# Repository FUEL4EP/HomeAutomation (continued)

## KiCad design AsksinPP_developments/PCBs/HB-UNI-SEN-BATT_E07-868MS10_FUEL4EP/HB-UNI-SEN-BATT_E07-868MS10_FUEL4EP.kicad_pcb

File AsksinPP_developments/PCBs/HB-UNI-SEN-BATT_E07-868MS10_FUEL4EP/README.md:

# HB-UNI-SEN-BATT_E07-868MS10_FUEL4EP  

**Platine für DIY AsksinPP Projekte basierend auf den folgenden möglichen Arduino-Modulen:**
- [Arduino Pro Mini 328 - 3.3V/8MHz](https://www.sparkfun.com/arduino-pro-mini-328-3-3v-8mhz.html): 32kByte Programmspeicher, 4kByte SRAM, 1kByte EEPROM
- NEU: [HB_Pro_Mini_ATMEGA1284P_FUEL4EP](https://github.com/FUEL4EP/HomeAutomation/tree/master/AsksinPP_developments/PCBs/HB_Pro_Mini_ATMEGA1284P_FUEL4EP)
	+ mit deutlich mehr Programm-, RAM- und EEPROM-Speicher als Arduino Pro Mini: 128kByte Programmspeicher, 16kByte SRAM, 4kByte EEPROM)
- [Tindie Pro Mini XL - v2 - ATmega 1284p](https://www.tindie.com/products/prominimicros/pro-mini-xl-v2-atmega-1284p/)
	+ mit deutlich mehr Programm-, RAM- und EEPROM-Speicher als Arduino Pro Mini: 128kByte Programmspeicher, 16kByte SRAM, 4kByte EEPROM)

## Credits

- diese Platine ist von Alexander Reinerts Platine [HB-UNI-SEN-BATT](https://github.com/alexreinert/PCB/tree/master/HB-UNI-SEN-BATT) abgeleitet.
- vielen Dank an Alexander Reinert für die Vorarbeit.

## Status der Validierung der Platine

- Platine wurde bis zur Version V1.3 bei JLCPCB erfolgreich gefertigt und validiert
- der Prototyp der neuen Platinenversion V1.4 wurde bei JLCPCB gefertigt, von Hand bestückt, verlötet und erfolgreich mit dem Sketch [HB-UNI-SENSOR1-AQ-BME680_KF_rLF](https://github.com/FUEL4EP/HomeAutomation/tree/master/AsksinPP_developments/sketches/HB-UNI-Sensor1-AQ-BME680_KF_rLF) validiert:
	
- Als Funkmodul wurde der [Adapter_EByte_E07_900MM10S_to_Ebyte_E07_868MS10_FUEL4EP](https://github.com/FUEL4EP/HomeAutomation/tree/master/AsksinPP_developments/PCBs/Adapter_EByte_E07_900MM10S_to_Ebyte_E07_868MS10_FUEL4EP) verwendet.

## Eigenschaften

- Weiterentwicklung von [HB-UNI-SEN-BATT](https://github.com/alexreinert/PCB/tree/master/HB-UNI-SEN-BATT) mit denselben Außenmaßen
- neue Eigenschaften:
	+ alternativ werden verschiedene Arduino Module unterstützt:
		- [Arduino Pro Mini 328 - 3.3V/8MHz](https://www.sparkfun.com/arduino-pro-mini-328-3-3v-8mhz.html): 32kByte Programmspeicher, 4kByte SRAM, 1kByte EEPROM
		- [HB_Pro_Mini_ATMEGA1284P_FUEL4EP](https://github.com/FUEL4EP/HomeAutomation/tree/master/AsksinPP_developments/PCBs/HB_Pro_Mini_ATMEGA1284P_FUEL4EP)
			+ mit deutlich mehr Programm-, RAM- und EEPROM-Speicher als Arduino Pro Mini: 128kByte Programmspeicher, 16kByte SRAM, 4kByte EEPROM)
			+ mit optionalem Boost-Konverter für Betrieb mit NiMH-Akkumulatoren oder nur einer AA Alkaline Battterie
		- [Tindie Pro Mini XL - v2 - ATmega 1284p](https://www.tindie.com/products/prominimicros/pro-mini-xl-v2-atmega-1284p/)
			+ mit deutlich mehr Programm-, RAM- und EEPROM-Speicher als Arduino Pro Mini: 128kByte Programmspeicher, 16kByte SRAM, 4kByte EEPROM

    + nur eine LED
    + dafür optionale Unterstützung von Akkumulatorbetrieb mit einem externen 'Huckepack' Aufwärtswandlermodul (siehe z.B. [HB-UNI-SENSOR1-CO2-SCD30](https://github.com/FUEL4EP/HomeAutomation/tree/master/AsksinPP_developments/sketches/HB-UNI-Sensor1-CO2_SCD30)
    + Stiftleiste J10 mit Versorgungsspannungen zum Gehäuseoberteil oder Akkulademodul
    + Korrektur der Abstandfehlers bei einem Batteriehalter. Beim [HB-UNI-SEN-BATT](https://github.com/alexreinert/PCB/tree/master/HB-UNI-SEN-BATT) hat das schon mal gerne zu thermischen Ausfällen durch mechanische Spannungen geführt.

### Benötigte Bauteile:
* eines der folgenden Arduino Module
	- [Arduino Pro Mini 328 - 3.3V/8MHz](https://www.sparkfun.com/arduino-pro-mini-328-3-3v-8mhz.html)
	- [HB_Pro_Mini_ATMEGA1284P_FUEL4EP](https://github.com/FUEL4EP/HomeAutomation/tree/master/AsksinPP_developments/PCBs/HB_Pro_Mini_ATMEGA1284P_FUEL4EP)
	- [Tindie Pro Mini XL - v2 - ATmega 1284p](https://www.tindie.com/products/prominimicros/pro-mini-xl-v2-atmega-1284p/)
*  [eByte E07-868MS10 Sendemodul 868MHz](https://www.elecbee.com/de-24376-E07-868MS10-CC1101-Stamp-Hole-Antenna-IoT-UHF-1000m-868MHz-SPI-10dBm-Wireless-Transmitter-Transceiver-RF-Module) oder alternativ das [Elecbee CC1101 Wireless-Modul 868 MHz](https://www.elecbee.com/de-24507-CC1101-Wireless-Module-868MHz-Digital-Transmission-Receiving-Industrial-grade-RF-Communication-Transparent-Transmission) Modul
* 1x LEDs 3mm Low Current (Pin 4)
* 1x 470Ohm Widerstände (Vorwiderstand für LED)
* Elko 10uF 1,5mm
* 2x Keystone 2460 Batteriehalter 1xAA (oder Goobay 1xAA Batteriehalter)
* Mikroschalter 6*6mm
* Stiftleiste RM 1.27mm 1x8 Pin (für eByte E07-868MS10 Modul)
* Stiftleisten RM 2,54mm (nach Bedarf)
* IRLU024N (optional für Verpolungsschutz)
* 100KOhm Widerstand (optional für Verpolungsschutz)
* 2x 10KOhm Widerstand (Pullup für I2C)

### Aufbauhinweise

- es wird dringend angeraten, vor dem Einbau der I2C Sensoren durchzuführen
    + einen Frequenztest. Hier der Frequenztest für einen [Tindie Pro Mini XL - v2 - ATmega 1284p](https://www.tindie.com/products/prominimicros/pro-mini-xl-v2-atmega-1284p/) : [FreqTest_1284P.ino](../Supplements/FreqTest_1284P/FreqTest_1284P.ino)
    + einen Leckstromtest. Hier der Leckstromtest für einen [Tindie Pro Mini XL - v2 - ATmega 1284p](https://www.tindie.com/products/prominimicros/pro-mini-xl-v2-atmega-1284p/) : [SleepTest_1284P.ino](../Supplements/SleepTest_1284P/SleepTest_1284P.ino)
        + der Leckstrom im Sleepmode sollte < 10 uA betragen
    + für einen Arduino Pro Mini die entsprechenden Standardsketche für den Frequenztest und den SleepTest verwenden.
    + am besten diese beiden Tests in einem Testaufbau mit Stecksockeln vor dem Einlöten durchführen

## Konfiguration der Überbrückungen

- bitte die Platinenüberbrückungen vor Inbetriebnahme je nach gewählter Hardwarekonfiguration wählen:

- die Tabellen dazu sind [hier](./Jumper_settings) zu finden
    
## lokale Installation des Github Releases auf Deinem Computer

- gehe bitte in Dein Zielinstallationsverzeichnis, wo Du mit der HB-UNI-SEN-BATT_E07-868MS10_FUEL4EP Platine mit KiCAD arbeiten möchtest

  - gebe dort 'git clone https://github.com/FUEL4EP/HomeAutomation.git' ein
	  + damit lädst Du mein [Sammelrepository](https://github.com/FUEL4EP/HomeAutomation) für alle meine auf Github freigegebenen HomeBrew Entwicklungen herunter.
  - dann findest Du ein neues Verzeichnis 'HomeAutomation' auf Deinem Rechner, das alle meine auf Github freigebenen Entwicklungen enthält, siehe [README.md](https://github.com/FUEL4EP/HomeAutomation/blob/master/README.md)
  	+ mache bitte regelmäßig ein Update mit 'git pull'
 -	die Platine HB-UNI-SEN-BATT_E07-868MS10_FUEL4EP findest Du unter './HomeAutomation/tree/master/AsksinPP_developments/PCBs/HB-UNI-SEN-BATT_E07-868MS10_FUEL4EP'
 
- alternativ kann vom Github [Sammelrepository](https://github.com/FUEL4EP/HomeAutomation) die ZIP-Datei HomeAutomation-master.zip heruntergeladen und auf dem lokalen Rechner ausgepackt werden. Bitte dann regelmäßig auf Github nach Updates schauen.

### Passende AsksinPP Projekte von FUEL4EP
- Arduino Pro Mini ATMega328P oder Tindie Pro Mini XL - v2 - ATmega 1284p basierend:
    + [HB-UNI-Sensor1-THPD-BME280](https://github.com/FUEL4EP/HomeAutomation/tree/master/AsksinPP_developments/sketches/HB-UNI-Sensor1-THPD-BME280)
    + [HB-UNI-Sensor1-TH-SHT75](https://github.com/FUEL4EP/HomeAutomation/tree/master/AsksinPP_developments/sketches/HB-UNI-Sensor1-TH-SHT75)
     + [HB-UNI-Sensor1-CO2_SCD30](https://github.com/FUEL4EP/HomeAutomation/tree/master/AsksinPP_developments/sketches/HB-UNI-Sensor1-CO2_SCD30)
- [HB_Pro_Mini_ATMEGA1284P_FUEL4EP](https://github.com/FUEL4EP/HomeAutomation/tree/master/AsksinPP_developments/PCBs/HB_Pro_Mini_ATMEGA1284P_FUEL4EP) oder [Tindie Pro Mini XL - v2 - ATmega 1284p](https://www.tindie.com/products/prominimicros/pro-mini-xl-v2-atmega-1284p/) basierend:
     + [HB-UNI-Sensor1-AQ-BME680](https://github.com/FUEL4EP/HomeAutomation/tree/master/AsksinPP_developments/sketches/HB-UNI-Sensor1-AQ-BME680)
    + [HB-UNI-Sensor1-AQ-BME680_KF](https://github.com/FUEL4EP/HomeAutomation/tree/master/AsksinPP_developments/sketches/HB-UNI-Sensor1-AQ-BME680_KF)
    + [HB-UNI-Sensor1-AQ-BME680_KF_DEBUG](https://github.com/FUEL4EP/HomeAutomation/tree/master/AsksinPP_developments/sketches/HB-UNI-Sensor1-AQ-BME680_KF_DEBUG)
    + [HB-UNI-Sensor1-RAD-AL53](https://github.com/FUEL4EP/HomeAutomation/tree/master/AsksinPP_developments/sketches/HB-UNI-Sensor1-RAD-AL53)
    + [HB-UNI-Sensor1-THPD-SHT85](https://github.com/FUEL4EP/HomeAutomation/tree/master/AsksinPP_developments/sketches/HB-UNI-Sensor1-THPD-SHT85)

### Passendes Gehäuse
* Camdenboss CBRS01SWH und CBRS01VWH
* oder [Gehäuse HB-UNI-SEN-BATT snap in V2 von wpatrick](https://www.thingiverse.com/thing:3540481) für 3D-Druck

### Hinweise
* Achtung: Kein Überspannungschutz vorhanden
* der Verpolungsschutz ist optional. Dafür Bauteil Q1 (IRLU024N) und R3 (100KOhm Widerstand) bestücken. Alternativ JP1 auf der Platinenrückseite überbrücken, um ohne Verpolungsschutz zu arbeiten.

### KiCAD Plugin
- für die Erzeugung der JLCPCB Produktionsdaten wurde das Plugin [KiCAD JLCPCB tools](https://github.com/bouni/kicad-jlcpcb-tools) verwendet.

## Bestellen von Platinen

- die Platine kann entweder direkt bei JLCPCB bestellt werden
- die notwendigen Produktionsdaten stehen [hier](./jlcpcb/production_files/)
- oder per PN bei [FUEL4EP](https://homematic-forum.de/forum/ucp.php?i=pm&mode=compose&u=20685) im Homematic Forum nachfragen. Aus der Bestellung der Prototypen sind noch Platinen kostengünstig abzugeben (Stand 13. Juli 2023).
	
## passende DIY I2C-Sensormodule für die Fertigung bei JLCPCB
- als DIY-Ersatz für kommerzielle Sensormodule stehen folgende passende Adapterplatinen zur Verfügung:
	- [I2C_Module_BME280_FUEL4EP](https://github.com/FUEL4EP/HomeAutomation/tree/master/AsksinPP_developments/PCBs/I2C_Module_BME280_FUEL4EP)
	- [I2C_Module_BME680_FUEL4EP](https://github.com/FUEL4EP/HomeAutomation/tree/master/AsksinPP_developments/PCBs/I2C_Module_BME680_FUEL4EP)
	- [I2C_Module_SHT85_BME280_FUEL4EP](https://github.com/FUEL4EP/HomeAutomation/tree/master/AsksinPP_developments/PCBs/I2C_Module_SHT85_BME280_FUEL4EP)
	- [I2C_Module_SHT45_BME280_FUEL4EP](https://github.com/FUEL4EP/HomeAutomation/tree/master/AsksinPP_developments/PCBs/I2C_Module_SHT45_BME280_FUEL4EP)
	- [4Bit_I2C_Port_Expander_Module_FUEL4EP](https://github.com/FUEL4EP/HomeAutomation/tree/master/AsksinPP_developments/PCBs/4Bit_I2C_Port_Expander_Module_FUEL4EP)

## Versionen
- KiCad Schaltplan-Editor Version: 8.0.9-8.0.9-0~ubuntu22.04.1, release build unter Kubuntu22.04.1
- KiCad Leiterplatteneditor Version: 8.0.9-8.0.9-0~ubuntu22.04.1, release build unter Kubuntu22.04.1 1.
- aktuelle PCB Version 1.4 
- aktuelle Schematics Version 1.3 

## Disclaimer

-  die Nutzung der hier veröffentlichten Inhalte erfolgt vollständig auf eigenes Risiko und ohne jede Gewähr.

## Lizenz 

**Creative Commons BY-NC-SA**<br>
Give Credit, NonCommercial, ShareAlike

<br />This work is licensed under a <a rel="license" href="http://creativecommons.org/licenses/by-nc-sa/4.0/">Creative Commons Attribution-NonCommercial-ShareAlike 4.0 International License</a>.

-EOF

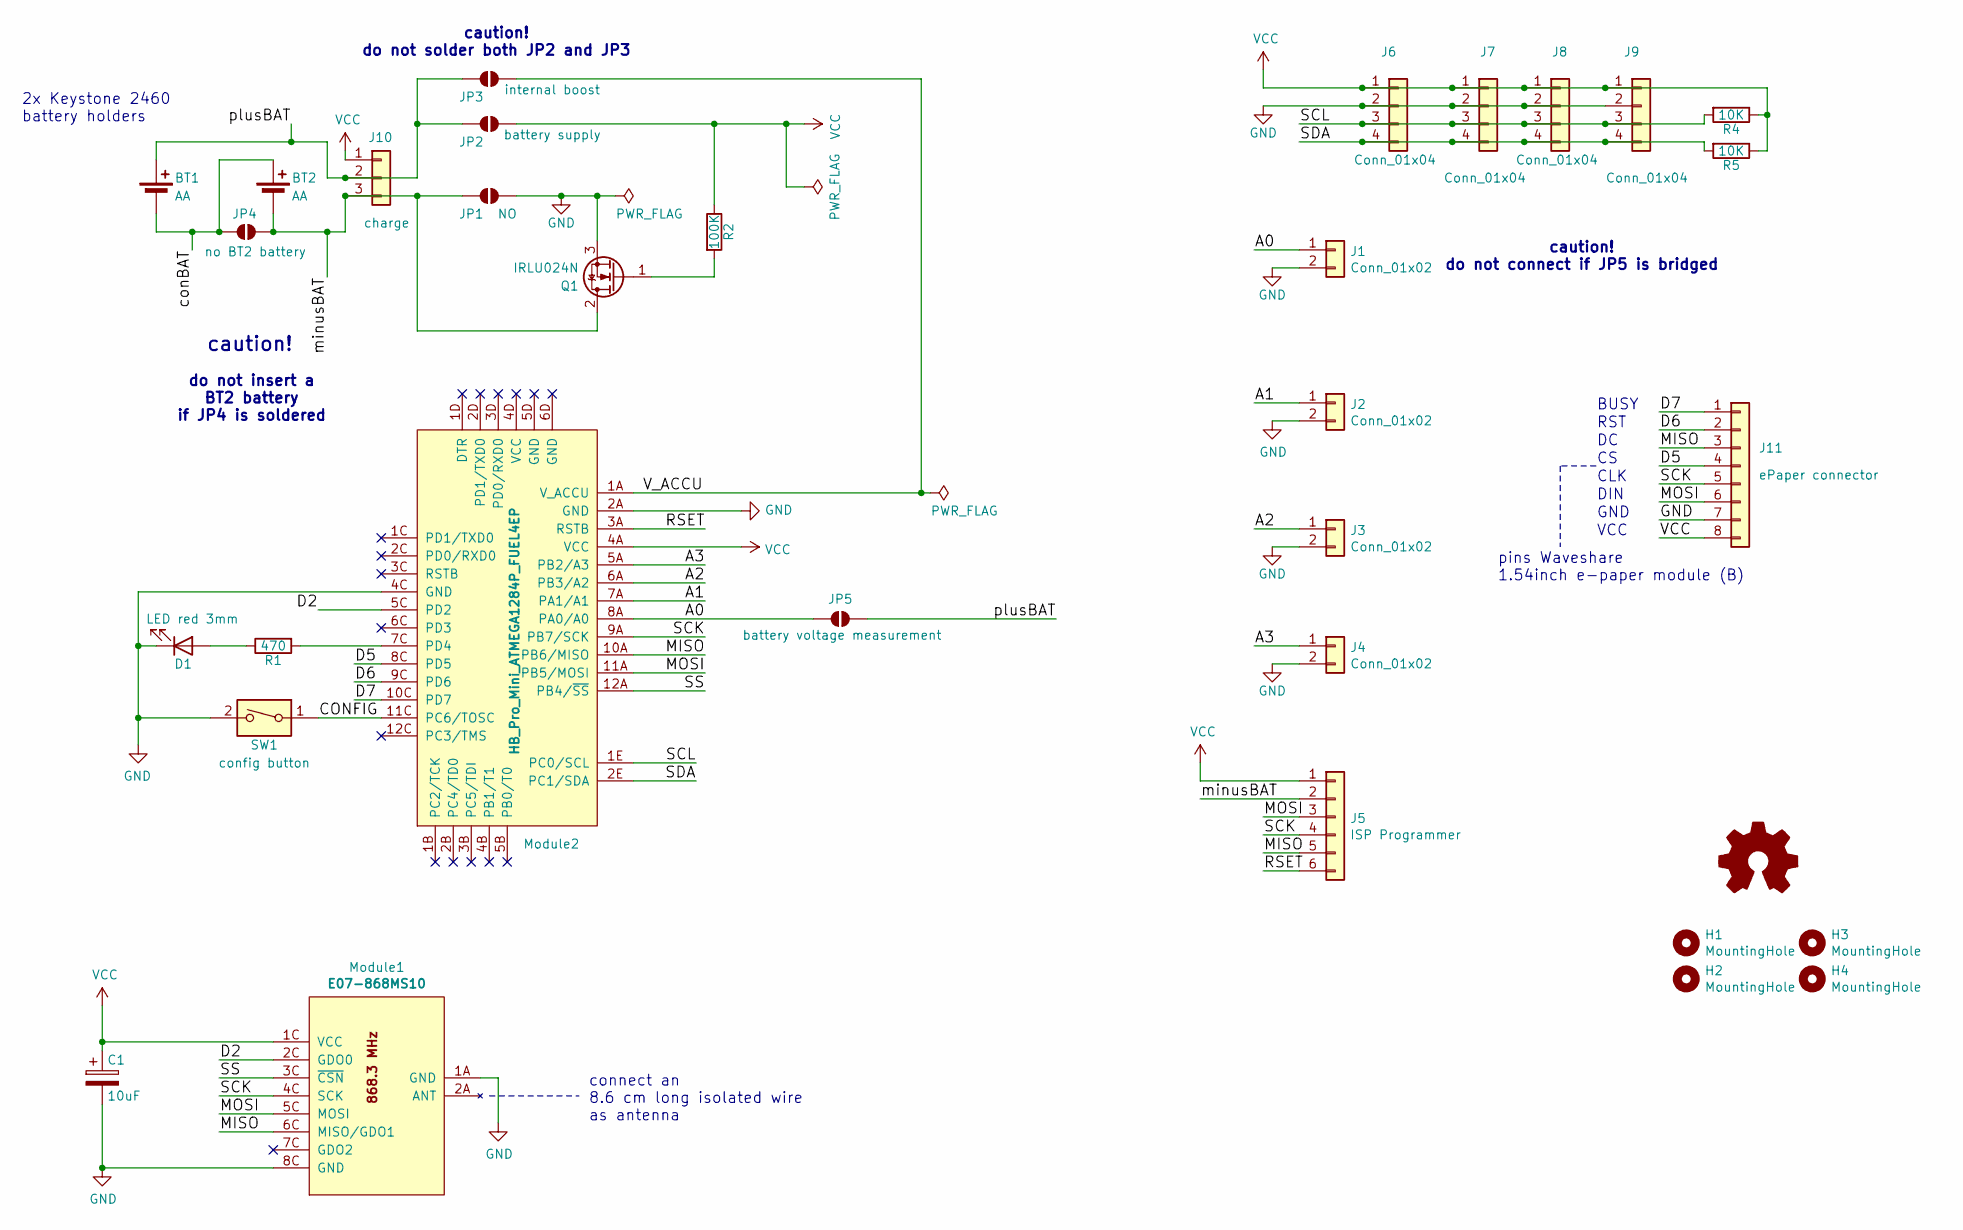
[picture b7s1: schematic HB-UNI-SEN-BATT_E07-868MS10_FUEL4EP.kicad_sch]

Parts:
BT1, BT2: AA; BatteryHolder_Keystone_2460_1xAA
C1: 10uF; CP_Radial_D4.0mm_P1.50mm
D1: LED red 3mm; LED_D3.0mm
H1, H2, H3, H4: MountingHole; MountingHole_2.2mm_M2_Pad_Via
J1, J2, J3, J4: Conn_01x02; PinHeader_1x02_P2.54mm_Vertical
J5: ISP Programmer; PinHeader_1x06_P2.54mm_Vertical
J6, J7, J8, J9: Conn_01x04; PinHeader_1x04_P2.54mm_Vertical
J10: charge; PinHeader_1x03_P2.54mm_Vertical
J11: ePaper connector; PinPads_1x08_P2.00mm_Vertical
JP1: NO; SolderJumper-2_P1.3mm_Open_Pad1.0x1.5mm
JP2: battery supply; SolderJumper-2_P1.3mm_Open_Pad1.0x1.5mm
JP3: internal boost; SolderJumper-2_P1.3mm_Open_Pad1.0x1.5mm
JP4: no BT2 battery; SolderJumper-2_P1.3mm_Open_Pad1.0x1.5mm
JP5: battery voltage measurement; SolderJumper-2_P1.3mm_Open_Pad1.0x1.5mm
LOGO1: Logo_Open_Hardware_Small; CC-BY-ND-SA
Module1: E07-868MS10; eByte_E07-868MS10
Module2: HB_Pro_Mini_ATMEGA1284P_FUEL4EP
Q1: IRLU024N; TO-251-3_Vertical
R1: 470; R_Axial_DIN0207_L6.3mm_D2.5mm_P2.54mm_Vertical
R2: 100K; R_Axial_DIN0207_L6.3mm_D2.5mm_P2.54mm_Vertical
R4, R5: 10K; R_Axial_DIN0207_L6.3mm_D2.5mm_P2.54mm_Vertical
SW1: config button; SW_PUSH_6mm_H5mm

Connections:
/A0: J1.1, JP5.1 (A), Module2.8A (PA0/A0)
/A1: J2.1, Module2.7A (PA1/A1)
/A2: J3.1, Module2.6A (PB3/A2)
/A3: J4.1, Module2.5A (PB2/A3)
/CONFIG: Module2.11C (PC6/TOSC), SW1.1
/D2: Module1.2C (GDO0), Module2.5C (PD2)
/D5: J11.4, Module2.8C (PD5)
/D6: J11.2, Module2.9C (PD6)
/D7: J11.1, Module2.10C (PD7)
/MISO: J5.5, J11.3, Module1.6C (MISO/GDO1), Module2.10A (PB6/MISO)
/MOSI: J5.3, J11.6, Module1.5C (MOSI), Module2.11A (PB5/MOSI)
/RSET: J5.6, Module2.3A (RSTB)
/SCK: J5.4, J11.5, Module1.4C (SCK), Module2.9A (PB7/SCK)
/SCL: J6.3, J7.3, J8.3, J9.3, Module2.1E (PC0/SCL), R4.2
/SDA: J6.4, J7.4, J8.4, J9.4, Module2.2E (PC1/SDA), R5.2
/SS: Module1.3C (~CSN), Module2.12A (PB4/~SS)
/V_ACCU: JP3.2 (B), Module2.1A (V_ACCU)
/conBAT: BT1.2 (-), BT2.1 (+), JP4.1 (A)
/minusBAT: BT2.2 (-), J5.2, J10.3, JP1.1 (A), JP4.2 (B), Q1.2 (D)
/plusBAT: BT1.1 (+), J10.2, JP2.1 (A), JP3.1 (A), JP5.2 (B)
GND: C1.2, D1.1 (K), J1.2, J2.2, J3.2, J4.2, J6.2, J7.2, J8.2, J9.2, J11.7, JP1.2 (B), Module1.1A (GND), Module1.8C (GND), Module2.2A (GND), Module2.4C (GND), Q1.3 (S), SW1.2
unnamed: D1.2 (A), R1.1
unnamed: Module2.7C (PD4), R1.2
unnamed: Q1.1 (G), R2.2
VCC: C1.1, J5.1, J6.1, J7.1, J8.1, J9.1, J10.1, J11.8, JP2.2 (B), Module1.1C (VCC), Module2.4A (VCC), R2.1, R4.1, R5.1

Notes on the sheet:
VCC
DIN
connect an 8.6 cm long isolated wire as antenna
BUSY
2x Keystone 2460 battery holders
GND
CLK
caution! do not connect if JP5 is bridged
caution!
RST
do not insert a BT2 battery if JP4 is soldered
caution! do not solder both JP2 and JP3
pins Waveshare 1.54inch e-paper module (B)

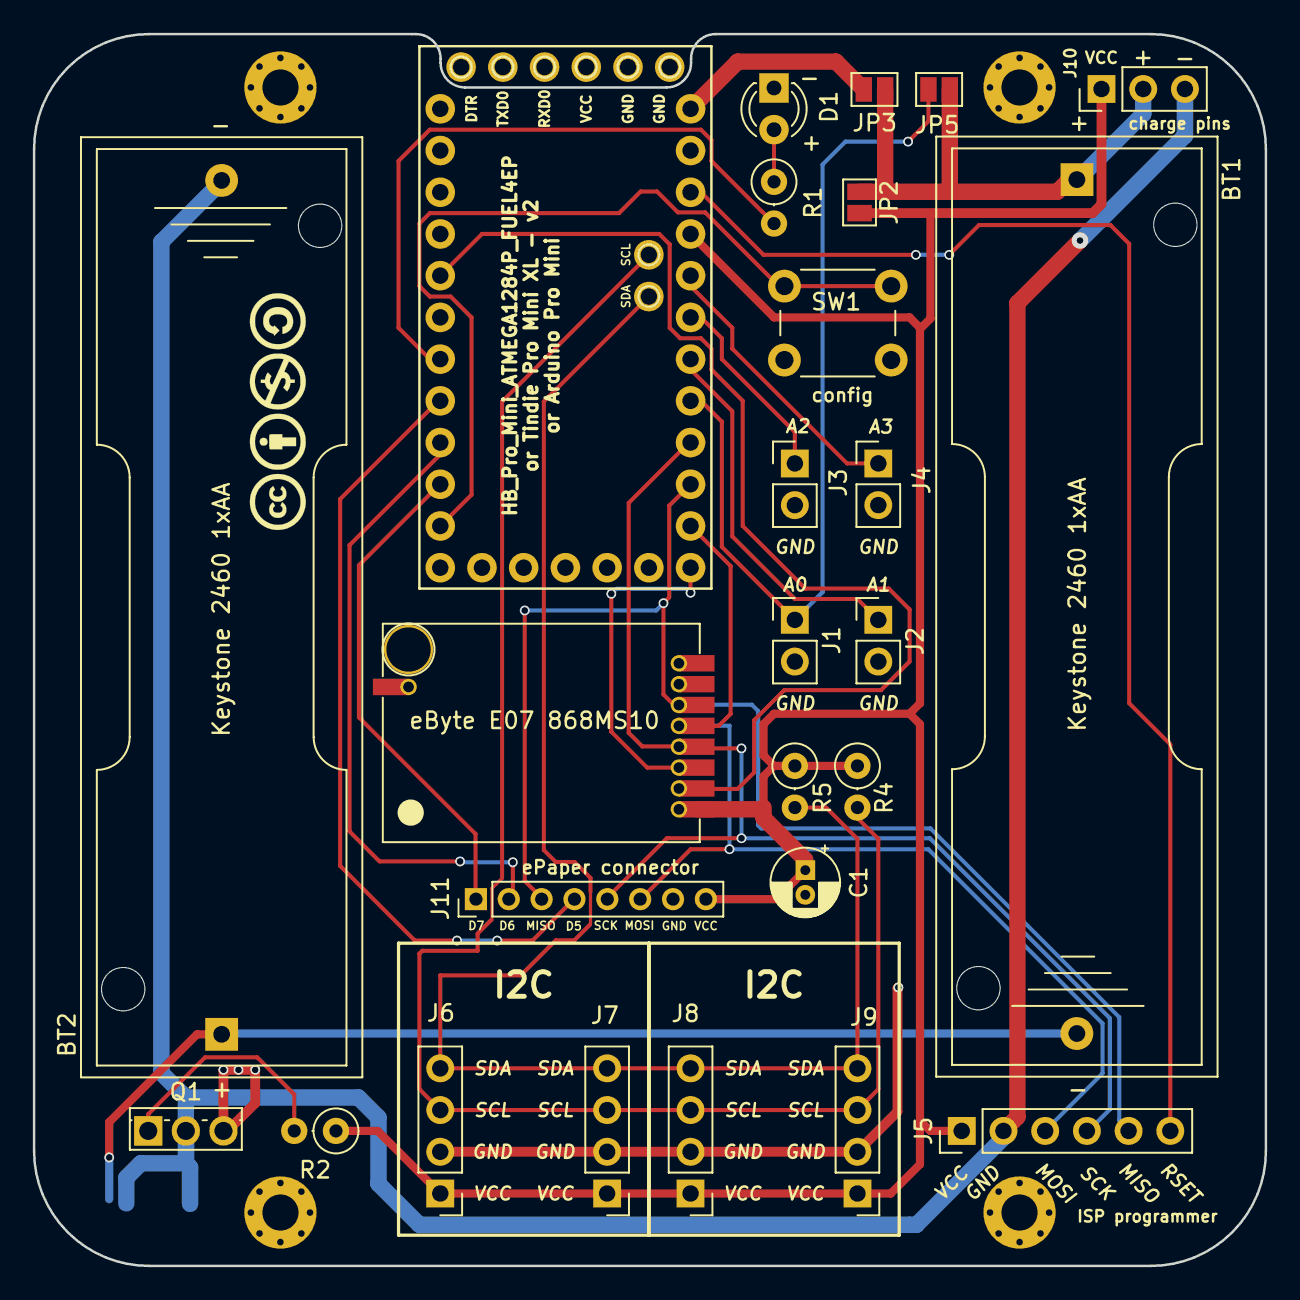
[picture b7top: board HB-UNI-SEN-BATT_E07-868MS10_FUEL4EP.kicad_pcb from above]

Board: 2 copper layers, 75.0 x 75.0 mm, 33 parts (0 on the bottom side), 25 nets.

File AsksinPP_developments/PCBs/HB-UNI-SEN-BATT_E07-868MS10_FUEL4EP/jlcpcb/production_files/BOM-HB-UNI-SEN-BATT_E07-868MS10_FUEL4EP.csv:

Comment,Designator,Footprint,LCSC,Quantity
LED red 3mm,D1,LED_D3.0mm,,1
Conn_01x02,J1,PinHeader_1x02_P2.54mm_Vertical,,1
Conn_01x02,J2,PinHeader_1x02_P2.54mm_Vertical,,1
Conn_01x04,J7,PinHeader_1x04_P2.54mm_Vertical,,1
AA,BT1,BatteryHolder_Keystone_2460_1xAA,,1
Conn_01x02,J3,PinHeader_1x02_P2.54mm_Vertical,,1
Conn_01x02,J4,PinHeader_1x02_P2.54mm_Vertical,,1
ISP Programmer,J5,PinHeader_1x06_P2.54mm_Vertical,,1
Conn_01x04,J6,PinHeader_1x04_P2.54mm_Vertical,,1
10uF,C1,CP_Radial_D4.0mm_P1.50mm,,1
10K,R4,R_Axial_DIN0207_L6.3mm_D2.5mm_P2.54mm_Vertical,,1
10K,R5,R_Axial_DIN0207_L6.3mm_D2.5mm_P2.54mm_Vertical,,1
470,R1,R_Axial_DIN0207_L6.3mm_D2.5mm_P2.54mm_Vertical,,1
IRLU024N,Q1,TO-251-3_Vertical,,1
Conn_01x04,J9,PinHeader_1x04_P2.54mm_Vertical,,1
charge,J10,PinHeader_1x03_P2.54mm_Vertical,,1
NO,JP1,SolderJumper-2_P1.3mm_Open_Pad1.0x1.5mm,,1
HB_Pro_Mini_ATMEGA1284P_FUEL4EP,Module2,HB_Pro_Mini_ATMEGA1284P_FUEL4EP,,1
E07-868MS10,Module1,eByte_E07-868MS10,,1
battery supply,JP2,SolderJumper-2_P1.3mm_Open_Pad1.0x1.5mm,,1
config button,SW1,SW_PUSH_6mm_H5mm,,1
Conn_01x04,J8,PinHeader_1x04_P2.54mm_Vertical,,1
MountingHole,H2,MountingHole_2.2mm_M2_Pad_Via,,1
MountingHole,H4,MountingHole_2.2mm_M2_Pad_Via,,1
MountingHole,H1,MountingHole_2.2mm_M2_Pad_Via,,1
MountingHole,H3,MountingHole_2.2mm_M2_Pad_Via,,1
Logo_Open_Hardware_Small,LOGO1,CC-BY-ND-SA,,1
ePaper connector,J11,PinPads_1x08_P2.00mm_Vertical,,1
AA,BT2,BatteryHolder_Keystone_2460_1xAA,,1
100K,R2,R_Axial_DIN0207_L6.3mm_D2.5mm_P2.54mm_Vertical,,1
battery voltage measurement,JP5,SolderJumper-2_P1.3mm_Open_Pad1.0x1.5mm,,1
no BT2 battery,JP4,SolderJumper-2_P1.3mm_Open_Pad1.0x1.5mm,,1
internal boost,JP3,SolderJumper-2_P1.3mm_Open_Pad1.0x1.5mm,,1

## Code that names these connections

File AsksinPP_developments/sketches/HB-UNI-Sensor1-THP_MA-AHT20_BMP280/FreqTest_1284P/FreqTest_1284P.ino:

//- -----------------------------------------------------------------------------------------------------------------------
// AskSin++
// 2016-10-31 papa Creative Commons - http://creativecommons.org/licenses/by-nc-sa/3.0/de/
// 2019-11-16 stan23 Creative Commons - http://creativecommons.org/licenses/by-nc-sa/3.0/de/
//- -----------------------------------------------------------------------------------------------------------------------

// define this to read the device id, serial and device type from bootloader section
// #define USE_OTA_BOOTLOADER

#define ATMega1284P

#if defined ARDUINO_ARCH_STM32F1
  #define STORAGEDRIVER at24cX<0x50,128,32>
  #define TICKS_PER_SECOND 500UL
  #define USE_HW_SERIAL
 
  #include <SPI.h>    // when we include SPI.h - we can use LibSPI class
  #include <Wire.h>   // for I2C access to EEPROM
  #include <EEPROM.h> // the EEPROM library contains Flash Access Methods
#endif

#include <AskSinPP.h>
#include <Device.h>
#include <Register.h>


#if defined ARDUINO_ARCH_STM32F1
  // we use a BluePill
  #define CC1101_GDO0_PIN     PB0
  #define CC1101_CS_PIN       PA4
  // CC1101 communication uses HW-SPI
  #define LED_PIN             LED_BUILTIN
#endif
#if defined ATMega1284P
// we use a ATMega 1284p Pro Mini XL
  #define CC1101_CS_PIN       4     // PB4
  #define CC1101_GDO0_PIN     10    // PD2
  #define CC1101_SCK_PIN      7     // PB7
  #define CC1101_MOSI_PIN     5     // PB5
  #define CC1101_MISO_PIN     6     // PB6
// ATMega 1284p LED
 #define LED_PIN             12     // PD4
#else
// we use a Pro Mini  
  #define CC1101_GDO0_PIN     2     // PD2
  #define CC1101_CS_PIN       10    // PB2
  #define CC1101_MOSI_PIN     11    // PB3
  #define CC1101_MISO_PIN     12    // PB4
  #define CC1101_SCK_PIN      13    // PB5
  // Pro Mini LED
  #define LED_PIN             4     // PD4
#endif

// all library classes are placed in the namespace 'as'
using namespace as;

// define all device properties
const struct DeviceInfo PROGMEM devinfo = {
    {0x01,0x01,0x01},       // Device ID
    "FreqTest00",           // Device Serial
    {0x00,0x00},            // Device Model
    0x10,                   // Firmware Version
    as::DeviceType::Sensor, // Device Type
    {0x00,0x00}             // Info Bytes
};

/**
 * Configure the used hardware
 */
#if defined ARDUINO_ARCH_STM32F1
typedef LibSPI<CC1101_CS_PIN> RadioSPI;
#else
//typedef AvrSPI<CC1101_CS_PIN, CC1101_MOSI_PIN, CC1101_MISO_PIN, CC1101_SCK_PIN> RadioSPI;
typedef AvrSPI<CC1101_CS_PIN, CC1101_MOSI_PIN, CC1101_MISO_PIN, CC1101_SCK_PIN> SPIType;
#endif
//typedef Radio<RadioSPI, CC1101_GDO0_PIN> RadioType;
typedef Radio<SPIType, CC1101_GDO0_PIN> RadioType;
typedef StatusLed<LED_PIN> LedType;
typedef AskSin<LedType,NoBattery,RadioType> HalType;



#define STARTFREQ 0x656A             // frequency we start scanning
#define MINFREQ (STARTFREQ - 0x300)  // frequency we abort scanning
#define SEARCHSTEP 0x50              // step with during search
#define BOUNDSTEP 0x10               // step width during upper/lower bound analysis


// see https://github.com/AskSinPP/asksinpp.de/blob/master/Grundlagen/FAQ/Fehlerhafte_CC1101.md
//#define ACTIVE_PING
HMID PING_FROM(0x6D,0xCC,0xC5);      // from address for status message e.g. switch
HMID PING_TO(0x19,0x57,0x4d);        // to address for status message / central / CCU
#ifdef ACTIVE_PING
  #define SCANTIME seconds2ticks(5)  // maximal time to wait for a valid message
#else
  #define SCANTIME seconds2ticks(60) // maximal time to wait for a valid message
#endif



class TestDevice : public Device<HalType,DefList0>, Alarm {
  DefList0 l0;
  uint16_t freq, start, end;
  uint8_t received, rssi;
public:
  enum SearchMode { Search, Up, Down, Done };
  SearchMode mode;
  HMID id;

  typedef Device<HalType,DefList0> BaseDevice;
  TestDevice (const DeviceInfo& i,uint16_t addr) : BaseDevice(i,addr,l0,0), Alarm(0), l0(addr),
      freq(STARTFREQ), start(STARTFREQ), end(STARTFREQ),
      received(0), rssi(0), mode(Search)  {}
  virtual ~TestDevice () {}

  virtual void trigger (__attribute__ ((unused)) AlarmClock& clock) {
    DPRINT("  ");DDEC(received);
    if (!received) {
      DPRINTLN("");
    } else {
      DPRINT(" / -");DDEC(rssi);DPRINTLN("dBm");
    }

    if( mode == Search ) {
      if( received > 0 ) {
        start = end = freq;
        mode = Up; // start find upper bound
        DPRINTLN("Search for upper bound");
        setFreq(freq + BOUNDSTEP);
      }
      else {
        if( freq < MINFREQ ) mode = Done;
        if( freq <= STARTFREQ ) setFreq(STARTFREQ + (STARTFREQ-freq) + SEARCHSTEP);
        else setFreq(STARTFREQ - (freq-STARTFREQ));
      }
    }
    else if(mode == Up) {
      if( received > 0 ) {
        end = freq;
        setFreq(end + BOUNDSTEP);
      }
      else {
        mode = Down; // start find lower bound
        DPRINTLN("Search for lower bound");
        setFreq(start - BOUNDSTEP);
      }
    }
    else if(mode == Down) {
      if( received > 0 ) {
        start = freq;
        setFreq(start - BOUNDSTEP);
      }
      else {
        mode = Done;
      }
    }
    if( mode == Done ) {
      DPRINT("\nDone: 0x21");DHEX(start);DPRINT(" - 0x21");DHEXLN(end);
      if( start == end && start == STARTFREQ ) {
        DPRINT("Could not receive any message");
      }
      else {
        freq = start+((end - start)/2);
        DPRINT("Calculated Freq: 0x21");DHEX((uint8_t)(freq>>8));DHEX((uint8_t)(freq&0xff));
        printFreq(0x210000 + freq);DPRINTLN("");

        // store frequency
        DPRINT("Store into config area: ");DHEX((uint8_t)(freq>>8));DHEX((uint8_t)(freq&0xff));
        StorageConfig sc = getConfigArea();
#if defined ARDUINO_ARCH_STM32F1
        Wire.begin();
        DPRINT(".");
#endif
        sc.clear();
        DPRINT(".");
        sc.setByte(CONFIG_FREQ1, freq>>8);
        DPRINT(".");
        sc.setByte(CONFIG_FREQ2, freq&0xff);
        DPRINT(".");
        sc.validate();

        DPRINTLN("stored!");
#if defined ARDUINO_ARCH_STM32F1
        // measurement is done, loop here forever
        while(1);
#else
        activity().savePower<Sleep<> >(this->getHal());
#endif
      }
    }
  }

  virtual bool process(Message& msg) {
    msg.from().dump(); DPRINT(".");
    rssi = max(rssi,radio().rssi());
    received++;
    if( received > 0 ) {
      trigger(sysclock);
    }
    return true;
  }

  bool init (HalType& hal) {
    this->setHal(hal);
    this->getDeviceID(id);
    hal.init(id);

    DPRINTLN("Start searching ...");
    setFreq(STARTFREQ);
    return false;
  }

  void setFreq (uint16_t current) {
    sysclock.cancel(*this);
    freq = current;
    rssi=0;
    received=0;
    DPRINT("Freq 0x21");DHEX(freq);
    printFreq(0x210000 + freq);
    DPRINT(": ");
    this->radio().initReg(CC1101_FREQ2, 0x21);
    this->radio().initReg(CC1101_FREQ1, freq >> 8);
    this->radio().initReg(CC1101_FREQ0, freq & 0xff);
    set(SCANTIME);
    sysclock.add(*this);
  }

  void printFreq(uint32_t freq) {
    char buffer[16];
    float val = (float)freq * 26.0 / 65536.0;
    dtostrf(val, 8, 3, buffer);
    DPRINT(buffer);DPRINT(" MHz");
  }
};

HalType hal;
TestDevice sdev(devinfo,0x20);

class InfoSender : public Alarm {
  class channel {
  public:
    uint8_t number() const {return 1; }
    uint8_t status() const {return 0; }
    uint8_t flags()  const {return 0; }
    void patchStatus(__attribute__ ((unused)) Message& msg) {}
    void changed(__attribute__ ((unused)) bool b) {}
  };
  uint8_t cnt;
  channel ch;
public:
  InfoSender () : Alarm(0), cnt(0) {}
  virtual ~InfoSender () {}

  virtual void trigger (AlarmClock& clock) {
#ifdef ACTIVE_PING
    InfoActuatorStatusMsg msg;
    msg.init(cnt++, ch, hal.radio.rssi());
    msg.to(PING_TO);
    msg.from(PING_FROM);
    msg.ackRequired();
    msg.setRpten();
    sdev.radio().write(msg,msg.burstRequired());
#endif
    sdev.led().ledOn(millis2ticks(100), 0);
    if( sdev.mode != TestDevice::SearchMode::Done ) {
      set(seconds2ticks(1));
      clock.add(*this);
    }
  }
} info;

void setup () {
#if defined ARDUINO_ARCH_STM32F1
  delay(5000);
#endif
  DINIT(38400,ASKSIN_PLUS_PLUS_IDENTIFIER);
  sdev.init(hal);
  // start sender
  info.trigger(sysclock);
}

void loop() {
  sdev.pollRadio();
  hal.runready();
}

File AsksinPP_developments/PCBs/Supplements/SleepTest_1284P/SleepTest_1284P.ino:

// ~~~~~~~~~~~~~~~~~~~~~~~~~~~~~~~~~~~~~~~~~~~~~~~~~~~~~~~~
// SleepTest (AVR Power-down Mode)
// 2019-01-22 Tom Major (Creative Commons)
// https://creativecommons.org/licenses/by-nc-sa/3.0/
// Clock Fuses: RC-Oszillator 8MHz, BOD off
// alternativ 8MHz Quarz an XTAL
//
// Der AVR wechselt mit diesem Sketch zwischen 10sec Aktiv Mode und 8sec power-down Mode mit Watchdog wakeup
// !! Falls mit der HW alles stimmt benötigt die Schaltung im power-down Mode nur ca. 4uA !!
//
// Auf die uA-Messung sollte man nur dann kurz umschalten wenn der AVR im power-down Mode ist (LED aus) und vor Ablauf der 8sec
// wieder zurück auf den mA-Messbereich. Andernfalls wird der AVR im aktivem Zustand eventuell nicht wieder anlaufen, da der Spannungsabfall
// dann über den uA-Messbereich des Multimeters zu hoch ist.
// ~~~~~~~~~~~~~~~~~~~~~~~~~~~~~~~~~~~~~~~~~~~~~~~~~~~~~~~~

#include <SPI.h>
#include "LowPower.h"

#define Tindie_m1284p

const int ledPin = 12;

void setup() 
{
    // cc1101_powerdown nur aktivieren falls wirklich ein CC1101 angeschlossen ist!
    cc1101_powerdown();
    pinMode(ledPin, OUTPUT);
}

void loop() 
{
    digitalWrite(ledPin, HIGH);
    delay(4000); 
    digitalWrite(ledPin, LOW);
    LowPower.powerDown(SLEEP_8S, ADC_OFF, BOD_OFF);  
}

// -------------------------------------------------------------------------
// CC1101 power down

#if defined Tindie_m1284p
  #define CC1101_GDO0        10           // PD2
  #define CC1101_CS_PIN       4           // PB4
#else // ATMega328P
  #define CC1101_GDO0         2           // GDO0 input interrupt pin
  #define CC1101_CS_PIN      10           // PB2
#endif

#define CC1101_SRES         0x30        // Reset CC1101 chip
#define CC1101_SIDLE        0x36        // Exit RX / TX, turn off frequency synthesizer and exit Wake-On-Radio mode if applicable
#define CC1101_SPWD         0x39        // Enter power down mode when CSn goes high

#define cc1101_Select()     digitalWrite(CC1101_CS_PIN, LOW)
#define cc1101_Deselect()   digitalWrite(CC1101_CS_PIN, HIGH)
#define wait_Miso()         while(digitalRead(MISO)>0)

void cc1101_powerdown()
{
  SPI.begin();                          // Initialize SPI interface
  pinMode(CC1101_GDO0, INPUT);          // Config GDO0 as input

  //reset();                            // Reset CC1101
  cc1101_Deselect();                    // Deselect CC1101
  delayMicroseconds(5);
  cc1101_Select();                      // Select CC1101
  delayMicroseconds(10);
  cc1101_Deselect();                    // Deselect CC1101
  delayMicroseconds(41);
  cc1101_Select();                      // Select CC1101

  wait_Miso();                          // Wait until MISO goes low
  SPI.transfer(CC1101_SRES);            // Send reset command strobe
  wait_Miso();                          // Wait until MISO goes low

  cc1101_Deselect();                    // Deselect CC1101
  // reset() end

  delay(100);
  
  //cmdStrobe(byte cmd) 
  cc1101_Select();                      // Select CC1101
  wait_Miso();                          // Wait until MISO goes low
  SPI.transfer(CC1101_SIDLE);           // Send strobe command
  cc1101_Deselect();                    // Deselect CC1101
  
  //cmdStrobe(byte cmd) 
  cc1101_Select();                      // Select CC1101
  wait_Miso();                          // Wait until MISO goes low
  SPI.transfer(CC1101_SPWD);            // Send strobe command
  cc1101_Deselect();                    // Deselect CC1101

  SPI.end();
  delay(10);
}

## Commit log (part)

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2021-12-08 HB-UNI-Sensor1-THPD-SHT85: fix corrupted documentation
2021-12-09 PCBs/HB-UNI-SenAct-4-4-SC_DS_FUEL4EP: small fixes; HB-UNI-Sensor1-THPD-SHT85: Small flaw detected: SYSCLK calibration is missing; Please wait a bit for a fix
2021-12-17 HB-UNI-Sensor1-THPD-SHT85: documentation update
2021-12-27 PCBs/HM-LC-Bl1-FM_FUEL4EP and PCBs/HB-UNI-SenAct-4-4-SC_DS_FUEL4EP: fixes, new V1.2 PCB layouts
2021-12-30 PCBs/HM-LC-Bl1-FM_FUEL4EP and PCBs/HB-UNI-SenAct-4-4-SC_DS_FUEL4EP: Update of README.md
2022-01-07 PCBs/HM-LC-Bl1-FM_FUEL4EP: Update of README.md
2022-01-08 tools/tmBattery_tmBatteryResDiv_calculator.ods update
2022-01-16 HB-UNI-Sensor1-THPD-SHT85: additional documentation / README.md update
2022-03-06 HB-UNI-Sensor1-THPD-BME280: fix of '#define PEERS_PER_CHANNEL 0' to '#define PEERS_PER_CHANNEL 6'
2022-03-16 HB-UNI-Sensor1-RAD-AL53: update README.md
2022-05-03 README.mds updates
2022-08-01 HB-UNI-Sensor1-AQ-BME680_KF: added battery measurement histogram over 10 months, reduced BAT_VOLT_LOW to 2.7V and BAT_VOLT_CRITICAL to 2.6V
2022-08-01 HB-UNI-Sensor1-RAD-AL53: fixed diagram labels
2022-08-02 hb-ep-devices-addon: updated README.md
2022-08-10 HB-UNI-Sensor1-RAD-AL53: documentation update, HM script improvement
2022-08-11 HB-UNI-Sensor1-RAD-AL53: additional links in README.md
2022-08-19 added ko-fi buttons for additionals README.mds[D[D[D
2022-09-06 HB-UNI-Sensor1-THPD-SHT85: Update of README.md
2022-09-11 HB-UNI-Sensor1-RAD-AL53: added method and first result of a radon measurement; HB-UNI-Sensor1-AQ-BME680_KF: added battery_voltage_over_11_months.png
2022-09-15 HB-UNI-Sensor1-RAD-AL53: added picture of Miele_vacuum_cleaner_adaptor_with_cotton_wool_pad.png
2022-09-21 HB-UNI-Sensor1-RAD-AL53: added radon measurement from cellar
2022-10-01 HB-UNI-Sensor1-AQ-BME680_KF: added Images/battery_voltage_over_12_months.png
2022-10-18 HB-UNI-Sensor1-THPD-SHT85: added 7days_moving_average_histogram.png
2022-12-11 HB-UNI-Sensor1-RAD-AL53: Update of README.md; added link to Radonhandbuch Deutschland of BfS"
2023-04-05 HB-UNI-Sensor1-CO2_SCD30: Fixes due to changed libraries; added possibility to compensate the increased annual average of CO2 concentration in the atmosphere due to the climate change
2023-05-10 HB-UNI-SEN-BATT_ATMega1284P_E07-868MS10_FRAM_FUEL4EP: Added pictures of JLCPCB prototype PCBs
2023-07-16 major update: hb-ep-devices-addon V1.14; added sketches HB-UNI-Sensor1-AQ-BME680_KF_rLF and HB-UNI-SenAct-4-4-SC_DS; migration of all PPCBs to KiCAD 6
2023-07-17 HB-UNI-SenAct-4-4-SC_DS_FUEL4EP: update README.md and added pictures
2023-07-17 HB-UNI-SenAct-4-4-SC_DS: Updates
2023-07-18 HB-UNI-SenAct-4-4-SC_DS_FUEL4EP: update of README.md
2023-07-20 README.md updates
2023-07-24 PCBs: KiCAD6 required improvements of layout data bases; added E07-900M10S into FUEL and footprint library
2023-07-25 PCBs: Fixes to ensure a proper production at JLCPCB, e.g. corrections of origins, rotations of assembled ICs etc.
2023-07-28 HB-UNI-SenAct-4-4-SC_DS: code cleanup and typo fixes
2023-08-02 HB-UNI-SenAct-4-4-SC_DS: update for avoiding a patch of AsksinPP / partial accu charging when accu voltage is low
2023-08-04 hb-ep-devices-addon: some fixes of wrong paths
2023-08-04 HB-UNI-SenAct-4-4-RC_DS: updated screen shots
2023-08-15 HB-UNI-SEN-BATT_ATMega1284P_E07-868MS10_FUEL4EP and HB-UNI-SEN-BATT_ATMega1284P_E07-868MS10_FRAM_FUEL4EP: Fix of wrong connection of EN pin of TPS61221 boost converter
2023-08-15 PCBs: moved origin to lower left corner in order to fit to JLCPCB's scheme
2023-08-25 CC1101_868MHz_RF_Modul_FUEL4EP: Update of README.md
2023-08-29 PCBs: CC1101_868MHz_RF_Modul_FUEL4EP, CC1101_868MHz_UFL_RF_Modul_FUEL4EP: improvements of layout and removal of castellated holes for cost reasons
2023-09-01 PCBs: CC1101_868MHz_RF_Modul_FUEL4EP, CC1101_868MHz_UFL_RF_Modul_FUEL4EP: update of silkscreen texts
2023-09-03 PCBs: Bit_I2C_Port_Expander_Module_FUEL4EP: Update of README.md
2023-09-07 PCBs: added I2C_Module_BME280_FUEL4EP
2023-09-08 PCBs: added I2C_Module_SHT85_BME280_FUEL4EP
2023-09-11 PCBs: added HB-UNI-SEN-BATT_E07-900MM10S_FUEL4EP, cleanup of obsolete files
2023-09-11 PCBs: fixed absolute library to relative library links
2023-09-11 PCBs/HB-UNI-SEN-BATT_E07-900MM10S_FUEL4EP: fixed frong screendump
2023-09-13 PCBs: added HB-UNI-SEN-BATT_ATMega1284P_E07-900MM10S_FUEL4EP; fies fixes for HB-UNI-SEN-BATT_ATMega1284P_E07-868MS10_FUEL4EP and HB-UNI-SEN-BATT_E07-900MM10S_FUEL4EP
2023-09-24 PCBs: update of README.mds; HB-UNI-SEN-BATT_ATMega1284P_E07-900MM10S_FUEL4EP: update of JLCPCB production data
2023-12-15 PCBs: added HB_TH_Sensor_SHT45_AllInOne_FUEL4EP
2023-12-16 PCB: I2C_Module_SHT85_BME280_FUEL4EP, I2C_Module_BME680_FUEL4EP: correction of connector placements in 3D view; 4Bit_I2C_Port_Expander_Module_FUEL4EP: change from 2N7000 to 2N7002K for SMD assembly
2024-01-07 PCBs: Updates due to order of some prototypes at JLCPCB
2024-01-14 PCBs: fix of some project specific KiCAD library paths for portability and missing PWR_FLGs for VCC in some schematics
2024-01-17 PCBs: updates for HB_Stamp_ATMega1284P_FUEL4EP and HB_TH_Sensor_SHT45_AllInOne_FUEL4EP; deletion of bak files
2024-01-21 PCBs: updates of HB_TH_Sensor_SHT45_AllInOne_FUEL4EP and HB_Stamp_ATMega1284P_FUEL4EP see README.mds
2024-02-09 PCBs: fix of I2C Pull-up resistors that were wrongly tied to GND
2024-02-14 PCBs: HB_Stamp_ATMega1284P_FUEL4EP: Realized pads for pogo pin adapter as ring
2024-02-14 README.md: added new devices and PCBs
2024-02-14 intermediate documentation update for new sensors
2024-02-15 README.md: typo fix
2024-02-16 I2C_Module_SHT45_BME280_small_FUEL4EP: documentation updates
2024-02-16 PCBs/I2C_Module_SHT45_BME280_small_FUEL4EP: documentation update
2024-02-17 PCBs: fixed documentation for tmBatteryResDiv / activations pin names were wrong
2024-03-04 HB-UNI-Sensor1-TH-SHT75: README.md / added link to replacement sketch HB-UNI-Sensor1-THD-SHT45
2024-03-06 updated documentation (case for HB-UNI-Sensor1-THPD-SHT45_BME280)
2024-03-06 case_HB-UNI-Sensor1-THPD-SHT45_BME280: picture update
2024-03-19 PCBs: HB-UNI-SEN-BATT_ATMega1284P_E07-868MS10_FRAM_FUEL4EP: changed validation status in README.md
2024-04-02 PCBs: first validation results of CC1101_868MHz_RF_Modul_FUEL4EP and CC1101_868MHz_UFL_RF_Modul_FUEL4EP
2024-04-02 PCBs: update of validation results of CC1101_868MHz_RF_Modul_FUEL4EP and CC1101_868MHz_UFL_RF_Modul_FUEL4EP: added RSSI sensitivities
2024-04-06 uodate of README.md
2024-04-06 sketches/FreqTest_range_test_with_distant_beacon: documentation updates
2024-04-11 sketches: HB-UNI-Sensor1-THD-SHT45 and HB-UNI-Sensor1-THPD-SHT45_BME280: fixes due to changes of Sensirion library
2024-04-24 sketches: FreqTest_range_test_with_distant_beacon: added hint how to increase frequency resolution of receive characteristics
2024-04-24 PCBs: 4Bit_I2C_Port_Expander_Module_FUEL4EP is now successfully validated; update of README.md; added pictures of prototype
2024-04-29 sketches: HB-UNI-Sensor1-THD-SHT45 and HB-UNI-Sensor1-THPD-SHT45_BME280: fixes due to changes of underlying Sensirion library
2024-05-07 PCBs: HB-UNI-SEN-BATT_ATMega1284P_E07-868MS10_FRAM_FUEL4EP: update of FRAM test
2024-05-27 PCBs: HB-UNI-SEN-BATT_ATMega1284P_E07-868MS10_FRAM_FUEL4EP: updated FRAM_test sketch
2024-06-04 update of AsksinPP_developments/addons/hb-ep-devices-addon/CCU_RM/AsksinPP_addon_files_generator/extract_rftypes_XML.groovy due to change of EQ3's libraries
2024-06-10 Updated HowTos documentation
2024-06-14 deleted fork AsksinPP_developments/libraries/Adafruit_FRAM_SPI
2024-06-14 updated README.md of PCB HB-UNI-SEN-BATT_ATMega1284P_E07-868MS10_FRAM_FUEL4EP
2024-06-16 deleted sketch HB-UNI-Sensor1-THPD_MA-AHT20_BMP280 due some detected bugs
2024-06-22 sketches/HB-UNI-Sensor1-THP_MA-AHT20_BMP280: documentation updates
2024-06-25 PCBs: updates to promote Adapter_EByte_E07_900MM10S_to_Ebyte_E07_868MS10_FUEL4EP in several PCBs
2024-06-26 sketches/HB-UNI-Sensor1-THP_MA-AHT20_BMP280: added measurement results of first 7 days as an example
2024-07-05 sketches/HB-UNI-Sensor1-THP_MA-AHT20_BMP280: updates of solar protection shield
2024-07-07 sketches/HB-UNI-Sensor1-THP_MA-AHT20_BMP280: delete construction data of inner radiation shield due to a necessary reconstruction
2024-07-15 release of new AsksinPP climate change observation sensor HB-UNI-Sensor1-THP_MA-AHT20_BMP280
2024-07-16 PCBs/HB_TH_Sensor_SHT45_AllInOne_FUEL4EP: update of 3D printable case; sketches/HB-UNI-Sensor1-THD-SHT45: update of battery discharge curve
2024-07-25 PCBs: CC1101_868MHz_RF_Modul_FUEL4EP and Adapter_EByte_E07_900MM10S_to_Ebyte_E07_868MS10_FUEL4EP: update of documentation
2024-09-13 PCBs/HB-UNI-SenAct-4-4-SC_DS_FUEL4EP: added control possibility by iPAD shortcuts
2024-09-18 sketches/HB-UNI-Sensor1-THP_MA-AHT20_BMP280: added documentation after 3 months of operation: moving averages and battery discharge
2024-09-25 PCBs/Adapter_EByte_E07_900MM10S_to_Ebyte_E07_868MS10_FUEL4EP: added validation results of prototype manufactured at JLCPCB
2024-09-26 PCBs/HB-UNI-SEN-BATT_ATMega1284P_E07-900MM10S_FUEL4EP: migration to KiCAD 8, LCSC fixes; PCBs/HB-UNI-SEN-BATT_ATMega1284P_E07-868MS10_FUEL4EP: BOM update
2024-09-29 PCBs/HB_Stamp_ATMega1284P_FUEL4EP: migration to KiCAD 8
2024-09-29 added PCBs/I2C_Module_BME680_small_FUEL4EP; corrected JLCPCB miinimum spacing in DRC rules
2024-09-30 PCBs/I2C_Module_SHT45_BME280_FUEL4EP und PCBs/I2C_Module_BME280_FUEL4EP: migration to KiCAD 8; fix of DRC rules for PCBs/I2C_Module_SHT45_BME280_FUEL4EP
2024-09-30 PCBs/CC1101_868MHz_UFL_RF_Modul_FUEL4EP: migration to KiCAD 8
2024-09-30 PCBs/HB-UNI-SEN-BATT_E07-900MM10S_FUEL4EP: migration to KiCAD 8
2024-10-01 PCBs/HB-UNI-SenAct-4-4-SC_DS_FUEL4EP: migration to KiCAD 8
2024-10-02 PCBs/I2C_Module_SHT45_BME280_FUEL4EP: documentation updates
2024-11-16 antennas: added 868.3MHz_DIY_dipole_antenna
2024-11-17 documentation updates for antennas
2024-11-19 antennas/README.md: added links for antenna theory
2024-12-16 sketches/HB-UNI-Sensor1-THPD-SHT45_BME280: added akku discharge curve after 8 months
2025-01-21 PCBs/HB-UNI-SenAct-4-4-SC_DS_FUEL4EP/Schematics: added erroneously deleted schematic drawings again
2025-02-16 PCBs/HB_Pro_Mini_ATMEGA1284P_FUEL4EP: added PCB HB_Pro_Mini_ATMEGA1284P_FUEL4EP as pre-release (not yet validated by a prototype)
2025-02-18 documentation update PCBs/HB_Stamp_IO_EXT_LEDs_Buttons_FUEL4EP/README.md
2025-02-27 PCBs: updated some JLCPCB manufacturing data after trial-order
2025-03-06 PCBs/HB_Pro_Mini_ATMEGA1284P_FUEL4EP and PCBs/I2C_Module_SHT45_BME280_small_FUEL4EP: updates based of prototype ordering at JLCPCB
2025-03-12 added Bots subdirectory for dummy counter
2025-03-17 sketches/HB-UNI-Sensor1-THPD-SHT45_BME280: update of >11 months accu operation time
2025-03-29 update of addons/hb-ep-devices-addon/README.md; delete obsolete folder sketches/HB-UNI-Sensor1-THP_MA-AHT20_BMP280/addon/hb-ep-devices-addon
2025-04-13 PCBs/HB_Stamp_IO_ATMega1284P_FUEL4EP and PCBs/HB_Stamp_IO_EXT_LEDs_Buttons_FUEL4EP: added pictures of prototypes
2025-04-14 PCBs/HB_Stamp_IO_EXT_LEDs_Buttons_FUEL4EP: documentation updates, LED solder helper added
2025-04-18 added PCBs/Adapter_noname_green_RF_module_to_Ebyte_E07_868MS10_FUEL4EP
2025-04-29 PCBs: update of prototype pictures that have been manufactured at JLCPCB
2025-05-07 PCBs: HB-UNI-SEN-BATT_E07-868MS10_FUEL4EP, HB-UNI-SEN-BATT_E07-900M10S_FUEL4EP, HB-UNI-SEN-BATT_E07-900MM10S_FUEL4EP, and HB-UNI-SEN-BATT_FUEL4EP: added prototype validation in README.md + pictures o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
2025-05-09 PCBs/HB_Stamp_IO_ATMega1284P_FUEL4EP: added test point TP3 (XTAL1)
2025-06-09 flipped back erroneously change Addon version number AsksinPP_developments/addons/hb-ep-devices-addon/CCU_RM/src/addon/VERSION
2025-06-26 fix of wrong link
2025-09-15 removed space at end of path AsksinPP_developments/antennas/868 MHz_FrSky_T_Dipolantenne_R9mini_R9MM
2025-10-06 update README.mds due to shortening of some filenames
2025-12-22 added avrdude example scripts for ATMega328P and Diamex Prog-S2 Programmer
2026-03-27 updated documentation for programming HB_Stamp_ATMega1284P_FUEL4EP with Diamex Prog S2 programmer

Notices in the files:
AsksinPP_developments/PCBs/HB-UNI-SEN-BATT_E07-868MS10_FUEL4EP/HB-UNI-SEN-BATT_E07-868MS10_FUEL4EP.kicad_sch:
fork of Alexander Reinert's HB-UNI-SEN-BATT/ Creative Commons License,non-commercial
AsksinPP_developments/PCBs/HB-UNI-SEN-BATT_E07-868MS10_FUEL4EP/README.md:
License: CC BY-NC-SA 4.0
